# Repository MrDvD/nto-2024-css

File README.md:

# НТО ЦСС 23/24

Репозиторий, который содержит в себе рабочие файлы команды _«Тернарный вопрос»_, созданные в процессе участия в _НТО ЦСС (23/24)_.

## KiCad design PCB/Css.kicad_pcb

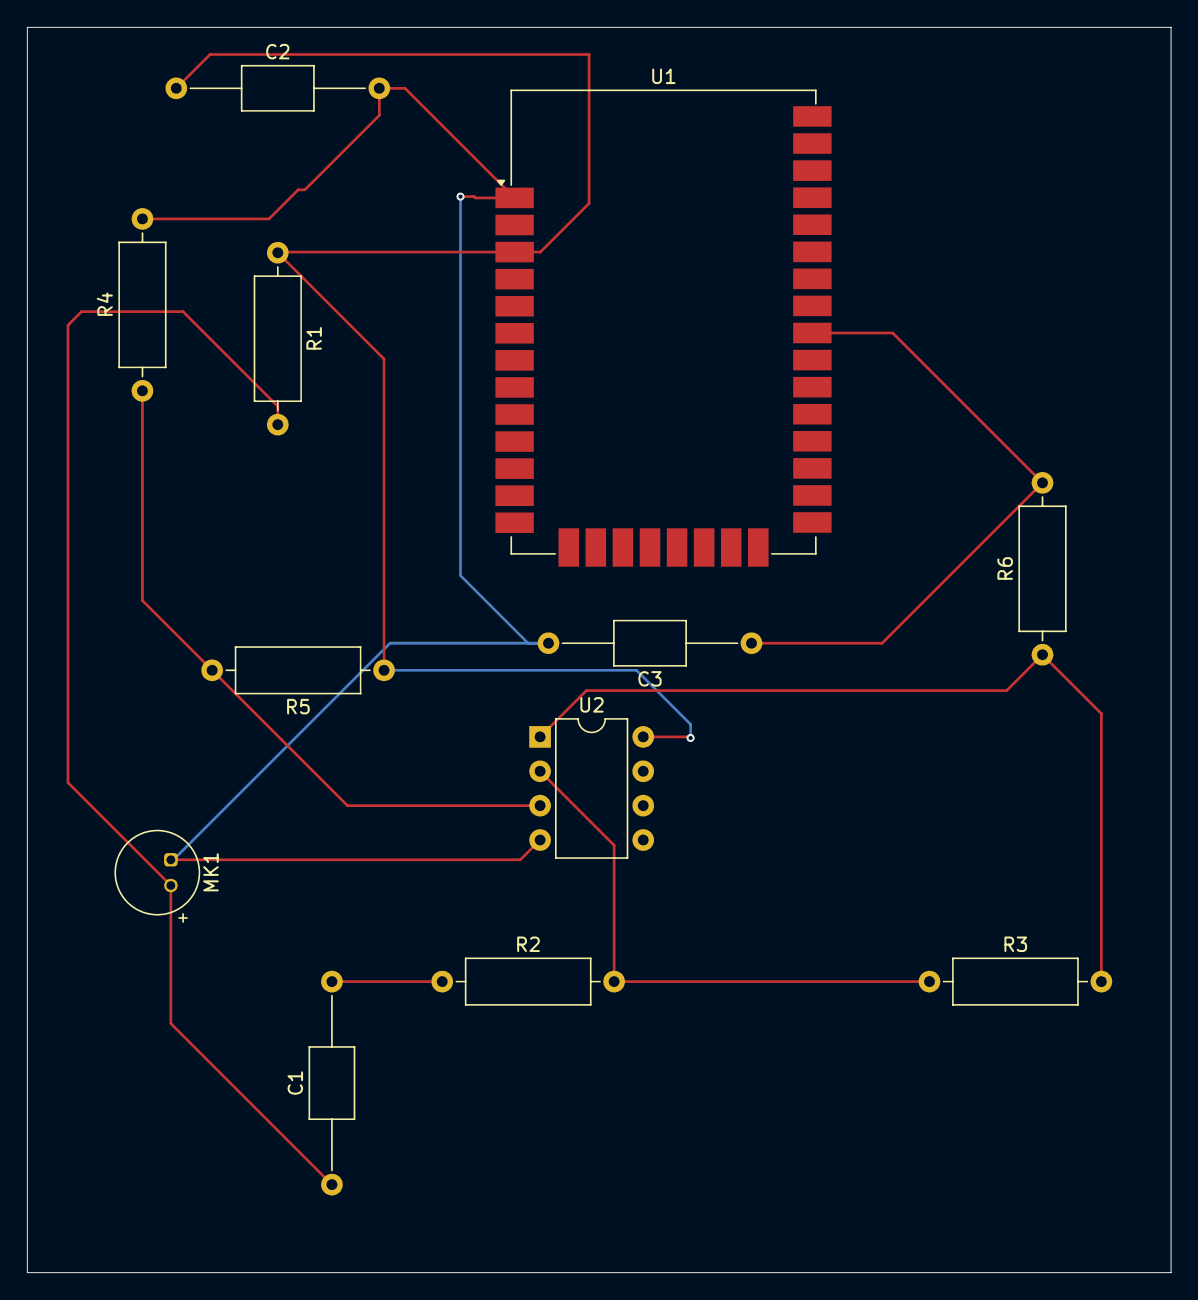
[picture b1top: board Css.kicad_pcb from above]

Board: 2 copper layers, 84.5 x 92.0 mm, 12 parts (0 on the bottom side), 8 nets.

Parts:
C1, C2, C3: 1uF; C_Axial_L5.1mm_D3.1mm_P15.00mm_Horizontal
MK1: Microphone_Condenser; POM-2244P-C3310-2-R
R1, R2: 1K; R_Axial_DIN0309_L9.0mm_D3.2mm_P12.70mm_Horizontal
R3: 100K; R_Axial_DIN0309_L9.0mm_D3.2mm_P12.70mm_Horizontal
R4, R5: 10K; R_Axial_DIN0309_L9.0mm_D3.2mm_P12.70mm_Horizontal
R6: 12K; R_Axial_DIN0309_L9.0mm_D3.2mm_P12.70mm_Horizontal
U1: ESP32-S3-MINI-1; Digi_XBee_SMT
U2: LM358; DIP-8_W7.62mm

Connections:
+5VA: C2.1, R1.1, R5.1, U1.3 (3V3), U2.8 (V+)
GND: C2.2, C3.2, MK1.1 (-), R4.2, U1.1 (GND), U1.2 (GND), U2.4 (V-)
unnamed: C1.2, R2.1
unnamed: C1.1, MK1.2 (+), R1.2
unnamed: R3.2, R6.1, U2.1
unnamed: R4.1, R5.2, U2.3 (+)
unnamed: R2.2, R3.1, U2.2 (-)
PIN 34: C3.1, R6.2, U1.29 (IO34)

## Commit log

2024-03-31 Queue example
2024-03-31 Timer
2024-04-01 sdlgnsdl
2024-04-01 Raspberry commit
2024-04-01 Memory
2024-04-01 Decibels change
2024-04-01 Tokens change + readme update
2024-04-01 Tokens fix
2024-04-01 Tokens fix #2
2024-04-02 Added task
2024-04-02 Something
2024-04-02 Something meh
2024-04-02 +- Works
2024-04-02 Server
2024-04-02 Plotting update + network instruction
2024-04-03 Some PCB changes
2024-04-03 Added plot class
2024-04-03 Should work
2024-04-03 Should work2
2024-04-03 Created website
2024-04-04 Intergrated Web interface
2024-04-04 Some changes
2024-04-04 Working GUI Activation
2024-04-04 IP change
2024-04-04 IP update
2024-04-04 Some --- changes
2024-04-04 Fix server
2024-04-04 Added finitav2
2024-04-04 Resolve conflict
2024-04-04 Files
2024-04-04 Files work
2024-04-04 Server update + fix
2024-04-05 Server update
2024-04-05 Finita
2024-04-05 Final server
2024-09-23 Trying to fix a mistake
